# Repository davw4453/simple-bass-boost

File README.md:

# simple-bass-boost
This is a simple one channel in-line bass boost circuit using the LM358 Op-amp. The circuit can be powered with around 5V. I made this circuit to enhance the sound of a cheap, no-name bluetooth speaker I had. 

I used this website as a reference for the design: https://electro-dan.co.uk/electronics/bassboost.aspx#single_supply_boost.

# Images

© 2026 David Wrinn. This work is licensed under CC BY-SA 4.0

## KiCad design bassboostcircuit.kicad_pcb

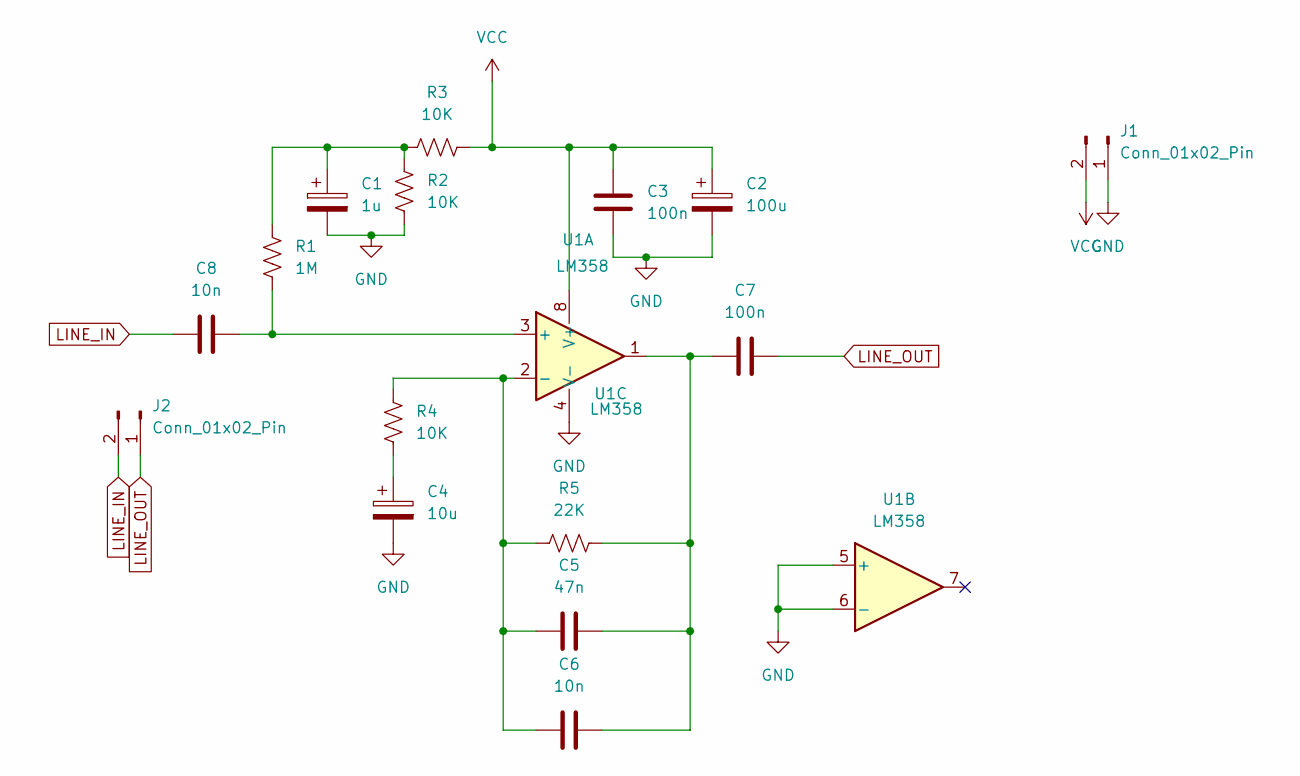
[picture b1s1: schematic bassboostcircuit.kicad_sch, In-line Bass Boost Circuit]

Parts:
C1: 1u; CP_Radial_D5.0mm_P2.00mm
C2: 100u; CP_Radial_D5.0mm_P2.00mm
C3, C7: 100n; C_Disc_D4.3mm_W1.9mm_P5.00mm
C4: 10u; CP_Radial_D5.0mm_P2.00mm
C5: 47n; C_Disc_D4.3mm_W1.9mm_P5.00mm
C6, C8: 10n; C_Disc_D4.3mm_W1.9mm_P5.00mm
J1, J2: Conn_01x02_Pin; PinHeader_1x02_P2.54mm_Vertical
R1: 1M; R_Axial_DIN0204_L3.6mm_D1.6mm_P5.08mm_Horizontal
R2, R3, R4: 10K; R_Axial_DIN0207_L6.3mm_D2.5mm_P10.16mm_Horizontal
R5: 22K; R_Axial_DIN0207_L6.3mm_D2.5mm_P10.16mm_Horizontal
U1: LM358; DIP-8_W7.62mm

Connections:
GND: C1.2, C2.2, C3.2, C4.2, J1.1, R2.2, U1.4 (V-), U1.5 (+), U1.6 (-)
LINE_IN: C8.1, J2.2
LINE_OUT: C7.2, J2.1
unnamed: C1.1, R1.1, R2.1, R3.1
unnamed: C4.1, R4.2
unnamed: C5.2, C6.2, C7.1, R5.2, U1.1
unnamed: C8.2, R1.2, U1.3 (+)
unnamed: C5.1, C6.1, R4.1, R5.1, U1.2 (-)
VCC: C2.1, C3.1, J1.2, R3.2, U1.8 (V+)

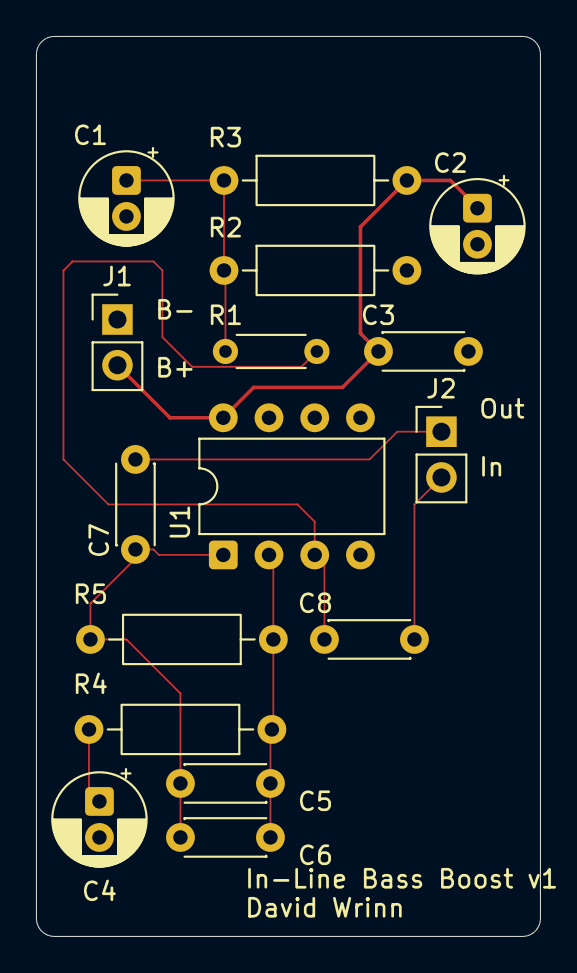
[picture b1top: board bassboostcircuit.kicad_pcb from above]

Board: 2 copper layers, 28.0 x 50.0 mm, 16 parts (0 on the bottom side), 9 nets.

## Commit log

2026-04-09 Initial Upload
2026-04-09 Fix image source in README
